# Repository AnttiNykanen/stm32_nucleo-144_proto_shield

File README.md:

# STM32 Nucleo-144 Prototyping Shield

Note: ~~I don't actually have a Nucleo-144 board at the moment and
haven't had this design manufactured yet.~~ ~~I haven't had time to check how the boards I had made turned out.~~ It seems like I have lost the boards while moving aparments. If you have manufactured some boards based on these files, please let me know if they fit.

This is a prototyping shield for ST's [Nucleo-144][stm32nucleo] development boards. It has the following features:

* Labeled breakout pins for the Morpho connectors. Differences between
  the various Nucleo boards are documented in [ST's User Manual][UM1974]
* 1.27mm pitch (SOIC) SMD prototyping area with two through-hole pads
  per SMD pad
* Through-hole prototyping area
* Four separate columns (2x9-pin and 2x10-pin) of uncommitted
  continuous pads that can be used for power rails and such.

[stm32nucleo]: http://www.st.com/web/catalog/tools/FM116/SC959/SS1532/LN1847?sc=stm32nucleo 
[UM1974]: http://www.st.com/st-web-ui/static/active/en/resource/technical/document/user_manual/DM00244518.pdf

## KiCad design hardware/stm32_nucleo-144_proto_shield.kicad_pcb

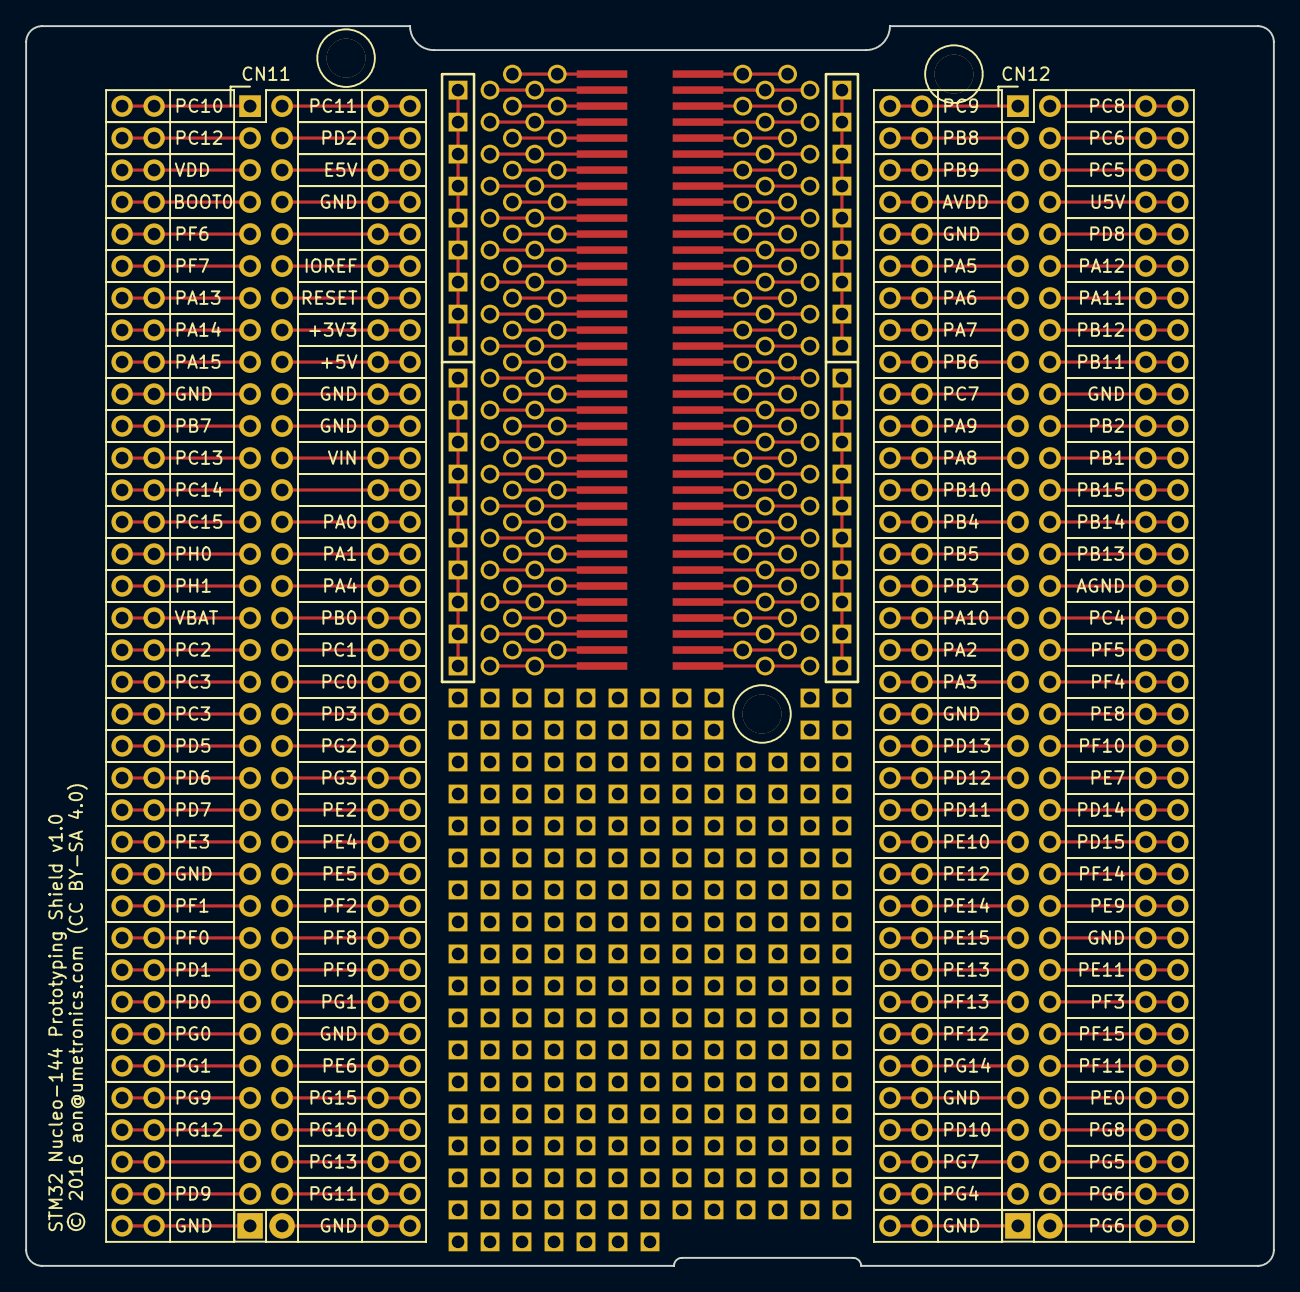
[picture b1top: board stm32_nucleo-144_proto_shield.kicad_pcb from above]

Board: 2 copper layers, 99.1 x 98.4 mm, 212 parts (0 on the bottom side), 130 nets.

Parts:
CN11, CN12: CONN_02X35; Pin_Header_Straight_2x35
P1, P2: CONN_01X02; Pin_Header_Straight_1x02
P3, P4, P5, P6, P7, P8, P9, P10, P11, P12, P13, P14, P15, P16, P17, P18, P19, P20, P21, P22, P23, P24, P25, P26, P27, P28, P29, P30, P31, P32, P33, P34, P35, P36, P37, P38, P39, P40, P41, P42, P43, P44, P45, P46, P47, P48, P49, P50, P51, P52, P53, P54, P55, P56, P57, P58, P59, P60, P61, P62, P63, P64, P65, P66, P67, P68, P69, P70, P71, P72, P73, P74, P75, P76, P77#19, P78, P79, P80, P81, P82, P83, P84, P85, P86, P87, P88, P89, P90, P91, P92, P93, P94, P95, P96, P97, P98, P99, P100, P101, P102, P103, P104, P105, P106, P107, P108, P109, P110, P111, P112, P113, P114, P115, P116, P117, P118, P119, P120, P121, P122, P123, P124, P125, P126, P127, P128, P129, P130, P131, P132, P133, P134, P135, P136, P137, P138, P139, P140, P141, P142, P143, P144, P145, P146: CONN_01X02; PROTOBOARD_CONN_2
P77, P77#2, P77#3, P77#4, P77#5, P77#6, P77#7, P77#8, P77#9, P77#10, P77#11, P77#12, P77#13, P77#14, P77#15, P77#16, P77#17, P77#18, P77#20: SOIC_AREA; PROTO_SOIC_AREA
PROTO_AREA: VAL**; PROTO_TH_AREA
PROTO_AREA#2, PROTO_AREA#3, PROTO_AREA#4, PROTO_AREA#5, PROTO_AREA#6, PROTO_AREA#7, PROTO_AREA#8, PROTO_AREA#9, PROTO_AREA#10, PROTO_AREA#11, PROTO_AREA#12, PROTO_AREA#13, PROTO_AREA#14, PROTO_AREA#15, PROTO_AREA#16, PROTO_AREA#17, PROTO_AREA#18, PROTO_AREA#19, PROTO_AREA#20, PROTO_AREA#21, PROTO_AREA#22, PROTO_AREA#23, PROTO_AREA#24, PROTO_AREA#25, PROTO_AREA#26, PROTO_AREA#27, PROTO_AREA#28, PROTO_AREA#29, PROTO_AREA#30, PROTO_AREA#31, PROTO_AREA#32, PROTO_AREA#33, PROTO_AREA#34, PROTO_AREA#35, PROTO_AREA#36, PROTO_AREA#37, PROTO_AREA#38, PROTO_AREA#39, PROTO_AREA#40, PROTO_AREA#41, PROTO_AREA#42, PROTO_AREA#43, PROTO_AREA#44, PROTO_AREA#45: VAL**; PROTO_TH_AREA

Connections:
/+3V3: CN11.16, P45.1, P45.2
/+5V: CN11.18, P46.1, P46.2
/AGND: CN12.32, P123.1, P123.2
/AVDD: CN12.7, P76.1, P76.2
/BOOT0: CN11.7, P6.1, P6.2
/E5V: CN11.6, P40.1, P40.2
/GND: CN11.8, CN11.19, CN11.20, CN11.22, CN11.49, CN11.60, CN12.9, CN12.20, CN12.39, CN12.54, CN12.63, P1.1, P1.2, P2.1, P2.2, P12.1, P12.2, P27.1, P27.2, P41.1, P41.2, P47.1, P47.2, P48.1, P48.2, P67.1, P67.2, P77#19.1, P77#19.2, P92.1, P92.2, P104.1, P104.2, P117.1, P117.2, P134.1, P134.2, P143.1, P143.2, P144.1, P144.2, P145.1, P145.2, P146.1, P146.2
/IOREF: CN11.12, P43.1, P43.2
/PA0: CN11.28, P51.1, P51.2
/PA1: CN11.30, P52.1, P52.2
/PA2: CN12.35, P90.1, P90.2
/PA3: CN12.37, P91.1, P91.2
/PA4: CN11.32, P53.1, P53.2
/PA5: CN12.11, P78.1, P78.2
/PA6: CN12.13, P79.1, P79.2
/PA7: CN12.15, P80.1, P80.2
/PA8: CN12.23, P84.1, P84.2
/PA9: CN12.21, P83.1, P83.2
/PA10: CN12.33, P89.1, P89.2
/PA11: CN12.14, P114.1, P114.2
/PA12: CN12.12, P113.1, P113.2
/PA13: CN11.13, P9.1, P9.2
/PA14: CN11.15, P10.1, P10.2
/PA15: CN11.17, P11.1, P11.2
/PB0: CN11.34, P54.1, P54.2
/PB1: CN12.24, P119.1, P119.2
/PB2: CN12.22, P118.1, P118.2
/PB3: CN12.31, P88.1, P88.2
/PB4: CN12.27, P86.1, P86.2
/PB5: CN12.29, P87.1, P87.2
/PB6: CN12.17, P81.1, P81.2
/PB7: CN11.21, P13.1, P13.2
/PB8: CN12.3, P74.1, P74.2
/PB9: CN12.5, P75.1, P75.2
/PB10: CN12.25, P85.1, P85.2
/PB11: CN12.18, P116.1, P116.2
/PB12: CN12.16, P115.1, P115.2
/PB13: CN12.30, P122.1, P122.2
/PB14: CN12.28, P121.1, P121.2
/PB15: CN12.26, P120.1, P120.2
/PC0: CN11.38, P56.1, P56.2
/PC1: CN11.36, P55.1, P55.2
/PC2: CN11.35, P20.1, P20.2
/PC3: CN11.37, P21.1, P21.2
/PC4: CN12.34, P124.1, P124.2
/PC5: CN12.6, P110.1, P110.2
/PC6: CN12.4, P109.1, P109.2
/PC7: CN12.19, P82.1, P82.2
/PC8: CN12.2, P108.1, P108.2
/PC9: CN12.1, P73.1, P73.2
/PC10: CN11.1, P3.1, P3.2
/PC11: CN11.2, P38.1, P38.2
/PC12: CN11.3, P4.1, P4.2
/PC13: CN11.23, P14.1, P14.2
/PC14: CN11.25, P15.1, P15.2
/PC15: CN11.27, P16.1, P16.2
/PD0: CN11.57, P31.1, P31.2
/PD1: CN11.55, P30.1, P30.2
/PD2: CN11.4, P39.1, P39.2
/PD3: CN11.40, P57.1, P57.2
/PD4: CN11.39, P22.1, P22.2
/PD5: CN11.41, P23.1, P23.2
/PD6: CN11.43, P24.1, P24.2
/PD7: CN11.45, P25.1, P25.2
/PD8: CN12.10, P112.1, P112.2
/PD9: CN11.69, P37.1, P37.2
/PD10: CN12.65, P105.1, P105.2
/PD11: CN12.45, P95.1, P95.2
/PD12: CN12.43, P94.1, P94.2
/PD13: CN12.41, P93.1, P93.2
/PD14: CN12.46, P130.1, P130.2
/PD15: CN12.48, P131.1, P131.2
/PE0: CN12.64, P139.1, P139.2
/PE1: CN11.61, P33.1, P33.2
/PE2: CN11.46, P60.1, P60.2
/PE3: CN11.47, P26.1, P26.2
/PE4: CN11.48, P61.1, P61.2
/PE5: CN11.50, P62.1, P62.2
/PE6: CN11.62, P68.1, P68.2
/PE7: CN12.44, P129.1, P129.2
/PE8: CN12.40, P127.1, P127.2
/PE9: CN12.52, P133.1, P133.2
/PE10: CN12.47, P96.1, P96.2
/PE11: CN12.56, P135.1, P135.2
/PE12: CN12.49, P97.1, P97.2
/PE13: CN12.55, P100.1, P100.2
/PE14: CN12.51, P98.1, P98.2
/PE15: CN12.53, P99.1, P99.2
/PF0: CN11.53, P29.1, P29.2
/PF1: CN11.51, P28.1, P28.2
/PF2: CN11.52, P63.1, P63.2
/PF3: CN12.58, P136.1, P136.2
/PF4: CN12.38, P126.1, P126.2
/PF5: CN12.36, P125.1, P125.2
/PF6: CN11.9, P7.1, P7.2
/PF7: CN11.11, P8.1, P8.2
/PF8: CN11.54, P64.1, P64.2
/PF9: CN11.56, P65.1, P65.2
/PF10: CN12.42, P128.1, P128.2
/PF11: CN12.62, P138.1, P138.2
/PF12: CN12.59, P102.1, P102.2
/PF13: CN12.57, P101.1, P101.2
/PF14: CN12.50, P132.1, P132.2
/PF15: CN12.60, P137.1, P137.2
/PG0: CN11.59, P32.1, P32.2
/PG1: CN11.58, P66.1, P66.2
/PG2: CN11.42, P58.1, P58.2
/PG3: CN11.44, P59.1, P59.2
/PG4: CN12.69, P107.1, P107.2
/PG5: CN12.68, P141.1, P141.2
/PG6: CN12.70, P142.1, P142.2
/PG7: CN12.67, P106.1, P106.2
/PG8: CN12.66, P140.1, P140.2
/PG9: CN11.63, P34.1, P34.2
/PG10: CN11.66, P70.1, P70.2
/PG11: CN11.70, P72.1, P72.2
/PG12: CN11.65, P35.1, P35.2
/PG13: CN11.68, P71.1, P71.2
/PG14: CN12.61, P103.1, P103.2
/PG15: CN11.64, P69.1, P69.2
/PH0: CN11.29, P17.1, P17.2
/PH1: CN11.31, P18.1, P18.2
/RESET: CN11.14, P44.1, P44.2
/U5V: CN12.8, P111.1, P111.2
/VBAT: CN11.33, P19.1, P19.2
/VDD: CN11.5, P5.1, P5.2
/VIN: CN11.24, P49.1, P49.2
unnamed: CN11.10, P42.1, P42.2
unnamed: CN11.26, P50.1, P50.2
unnamed: CN11.67, P36.1, P36.2

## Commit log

2016-01-19 initial revision

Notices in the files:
hardware/stm32_nucleo-144_proto_shield.kicad_pcb:
CC BY-SA 4.0
© 2016 aon@umetronics.com (CC BY-SA 4.0)
